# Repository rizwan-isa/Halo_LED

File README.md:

[comment]: <> (GitHub Repository Display Page)
[comment]: <> (Engineering Services Templates)
[comment]: <> (Rizwan Isa, 2024)

# Engineering Services — Project Templates

This repository contains reusable templates, skeletons, and process assets used by **Engineering Services** for delivering professional electronics, PCB, and mechanical CAD projects.

It is intended to:

- standardise project structure across client and personal work
- reduce setup time for new projects
- improve consistency of documentation, reviews, and manufacturing outputs
- make projects easy to navigate, audit, and hand over

---

## What’s Included

### Project Skeletons

Ready-made folder structures for common project types (e.g. hardware PCB project).

### Documentation Templates

Reusable documents for requirements capture, design notes, design reviews, and manufacturing handover.

### Gitignore Templates

Tool-specific `.gitignore` templates (KiCad, Altium, CAD exports) to keep repos clean and professional.

### Checklists

Practical checklists for:

- design readiness
- review readiness
- release readiness / manufacturing handover

---

## How To Use This Repo

### Recommended: Start a New Project From a Skeleton

1. Copy a skeleton into your new project workspace (example below).
2. Create a new Git repository for the project (one repo per project).
3. Commit the initial structure and start work.

Example (hardware PCB project):

```bash
# From your workspace
cp -R ~/EngineeringServices/01_Templates/engineering-services-templates/project_skeletons/hardware_project \
      ~/EngineeringServices/02_Freelance/Client_Project

cd ~/EngineeringServices/02_Freelance/Client_Project
git init
git add .
git commit -m "Initial project structure"
```

# KiCad Template – Local KiBot “Review Datapack” workflow

This repo is set up to generate a **Review Datapack** (PDFs, BoMs, Gerbers, drill files, etc.) using **KiBot**, driven by a **GitHub Actions workflow**.  
You can run the same workflow **locally** using [`act`](https://github.com/nektos/act) (which runs GitHub Actions inside Docker).

This README documents the **exact local workflow** we used, the **diagnostic steps**, and the **fixes** applied so the workflow runs end‑to‑end locally.

---

## Repo layout (relevant bits)

- `.github/workflows/gen_outputs.yml`  
  GitHub Actions workflow that runs KiBot + packages outputs into a datapack.
- `src/config.kibot.yaml`  
  Main KiBot config entrypoint.
- `src/kibot/test.yaml`  
  “Collector” config that imports all outputs. You can comment out imports here to debug.
- `src/kibot/outputs/*.yaml`  
  Individual KiBot output definitions (Gerbers, drill, BoM, PDFs, etc.).
- `KiBotOutput/`  
  Output folder created by the workflow.
- `ReviewDatapack/`  
  Final datapack folder created by the workflow.

---

## Prerequisites (local)

### 1) Docker

- Install Docker Desktop and ensure it’s running.

### 2) act

On macOS:

```bash
brew install act
```

Check it works:

```bash
act --version
docker --version
```

> **Note (Apple Silicon / M1/M2/M3):**  
> `act` may run containers as `arm64` by default. If you ever hit image compatibility issues, you can force:
>
> ```bash
> act --container-architecture linux/amd64 ...
> ```

---

## Quick start (run the workflow locally)

From the repo root:

```bash
act -W .github/workflows/gen_outputs.yml -j GRD
```

Typical useful variations:

```bash
# Re-run without rebuilding everything (often faster)
act -W .github/workflows/gen_outputs.yml -j GRD -r

# If you need amd64 on Apple Silicon
act -W .github/workflows/gen_outputs.yml -j GRD --container-architecture linux/amd64
```

After success, you should have:

- `KiBotOutput/` populated (PDFs, BoMs, Gerbers, drill files, logs, etc.)
- `ReviewDatapack/Datapack_<...>/` populated (packaged datapack structure)

---

## How the KiBot configuration is wired

### Main entrypoint

`src/config.kibot.yaml` imports:

- `kibot/test.yaml`

### Collector / “test” config

`src/kibot/test.yaml` imports many outputs, e.g.

- `outputs/archive_prj.yaml`
- `outputs/drill.yaml`
- `outputs/gerbers.yaml`
- `outputs/pdf_schematic.yaml`
- etc.

**Debug tip:** you can comment out outputs to isolate problems.

Example (disabling 3D output while debugging):

```yaml
import:
  - outputs/pcb_2d.yaml
  # - outputs/pcb_3d.yaml   # disabled for debug
  - outputs/pdf_pcb.yaml
```

---

## Step-by-step diagnostics & fixes (what we actually did)

### Step 1 — Confirm where KiBot logs are written

We saw the workflow failing at:

- **“Copy kibot run log file into Reports folder”**  
  with:
  ```
  cp: cannot stat 'kibot_log.log': No such file or directory
  ```

**Diagnosis commands (local):**

```bash
ls -al
ls -al KiBotOutput || true

# Find any kibot logs/debug output that actually exists
find . -maxdepth 3 -type f \( -iname "*kibot*log*" -o -iname "*kibot*debug*" \) -print
```

What we found:

- `KiBotOutput/kibot_debug.log` existed
- `KiBotOutput/kibot_log.log` did **not** exist yet

**Fix applied (in workflow):**  
Make KiBot write an explicit log file that the later `cp` step expects.

In `.github/workflows/gen_outputs.yml` we ensured the KiBot step includes:

```yaml
additional_args: "-d -vv -L KiBotOutput/kibot_log.log"
```

Now the copy step succeeds because the file exists:

- `KiBotOutput/kibot_log.log`

> If you prefer not to use `-L`, an alternative is redirecting output, e.g.  
> `kibot ... |& tee KiBotOutput/kibot_log.log` (when running KiBot directly).

---

### Step 2 — Diagnose KiBot config errors (missing output type)

We hit this KiBot error in `KiBotOutput/kibot_debug.log`:

```
ERROR: Output `Run KiBot` needs a type
```

That error means:

- KiBot parsed an entry under `outputs:` where `name:` existed but `type:` was missing.

**How we inspected the exact location:**

```bash
# Show the section around the error
nl -ba KiBotOutput/kibot_debug.log | sed -n '460,520p'

# See config/import chain in the log
grep -nE "Using configuration file|Parsing imports|Outputs loaded from" KiBotOutput/kibot_debug.log | tail -n 80
```

**How to find the broken output in your repo:**

```bash
# Search for the output name (example)
grep -RIn "Run KiBot" src/kibot

# Search for any output missing a type (quick manual check)
grep -RIn "^\s*-\s*name:" src/kibot
```

**What to fix:** ensure every output has a `type:`.

Correct pattern:

```yaml
outputs:
  - name: "something"
    type: "pdf" # <- must exist
```

> If you still can’t find it, a YAML indentation error (or accidentally importing a non‑KiBot YAML) can cause odd parsing.  
> In that case, temporarily comment out imports in `src/kibot/test.yaml` until the error disappears, then narrow down.

---

### Step 3 — Fix `upload-artifact` failures when running locally with act

Once the datapack generation was working, the job still failed at:

- **“Archive production artifacts”** using `actions/upload-artifact@v4`

Errors seen included:

- `Unable to get the ACTIONS_RUNTIME_TOKEN env variable`
- `Failed to CreateArtifact ... ECONNREFUSED`

**Root cause:**  
`act` is not GitHub Actions. `upload-artifact` expects GitHub’s artifact service + runtime token, which does not exist locally.

**Fix applied (Option A):**  
Skip the upload step when running under `act` using `env.ACT` (act sets this).

In `.github/workflows/gen_outputs.yml`:

```yaml
- name: Archive production artifacts
  if: ${{ !env.ACT }}
  uses: actions/upload-artifact@v4
  with:
    name: ReviewDatapack
    path: ReviewDatapack
```

✅ With this change, local runs complete successfully and you just take the files from `ReviewDatapack/` yourself.

---

## Common shell gotchas (zsh)

### Inline comments need a space

This fails:

```bash
ls# comment
```

Use:

```bash
ls # comment
```

### Parentheses in `find`

In zsh, parentheses should be escaped:

```bash
find . -maxdepth 3 -type f \( -iname "*kibot*log*" -o -iname "*kibot*debug*" \) -print
```

---

## Where to change things

### Change project metadata used in the workflow

Edit `.github/workflows/gen_outputs.yml` `env:` section, e.g.:

- `BaseFileName`
- `PCBANumber`
- `PCBNumber`
- `Timezone`

### Enable/disable specific KiBot outputs

Edit `src/kibot/test.yaml` import list and comment out modules you don’t want (or while debugging).

---

## Verify outputs

After a local run:

```bash
ls -al KiBotOutput
ls -al ReviewDatapack
```

Typical important files:

- PDFs: schematic / assembly docs
- Manufacturing: gerbers, drill
- BoMs: CSV + HTML
- Logs: `KiBotOutput/kibot_debug.log`, `KiBotOutput/kibot_log.log`

---

## Troubleshooting checklist

1. **Workflow fails copying a file**

- Run `find` to confirm the file exists and path matches.
- Fix the workflow to point at the real file path.

2. **KiBot complains about config**

- Read `KiBotOutput/kibot_debug.log`
- Use `nl -ba ... | sed -n '...p'` around the error
- Narrow down by commenting out imports in `src/kibot/test.yaml`

3. **upload-artifact fails locally**

- Confirm the step is guarded with:
  ```yaml
  if: ${{ !env.ACT }}
  ```

---

## Appendix — Running KiBot manually (optional)

If you want to run KiBot directly (outside GitHub Actions), from repo root:

```bash
kibot -c src/config.kibot.yaml -d -vv -L KiBotOutput/kibot_log.log
```

> This requires KiBot installed on your machine (the workflow does not).

# Local Workflow Notes (Detailed)

This file is a “deep dive” version of the local run instructions from the root README.

## 1) Install tools

### macOS (Homebrew)

```bash
brew install act
brew install --cask docker
```

Start Docker Desktop, then:

```bash
docker info
act --version
```

## 2) Run the GRD job

```bash
act -W .github/workflows/gen_outputs.yml -j GRD
```

## 3) Inspect results

```bash
tree -L 2 KiBotOutput || ls -R KiBotOutput
tree -L 3 ReviewDatapack || ls -R ReviewDatapack
```

## 4) Debug KiBot problems fast

### A) Confirm config + import chain

```bash
grep -nE "Using configuration file|Parsing imports|Outputs loaded from" KiBotOutput/kibot_debug.log | tail -n 80
```

### B) Show the error context

```bash
nl -ba KiBotOutput/kibot_debug.log | sed -n '1,140p'
```

### C) Binary search outputs

Edit `src/kibot/test.yaml` and comment out half the imports; rerun; repeat until you isolate the failing output module.

## 5) Why we skip artifact upload locally

`actions/upload-artifact@v4` needs GitHub’s runtime token and artifact service.  
`act` doesn’t provide that, so we guard the step:

```yaml
if: ${{ !env.ACT }}
```

This is the correct approach for local debug and CI parity:

- CI run on GitHub uploads artifacts
- Local run produces artifacts on disk only

---

## Creating a new project from this template

### Option 1: GitHub UI (recommended)

1. On GitHub, click **Use this template**
2. Create the new repository (e.g. `FFM`)
3. Clone it locally

```bash
git clone <your-new-repo-url>
cd <your-new-repo>
```

4. Initialize/rename the project (this updates filenames AND workflow env vars)

```bash
python3 scripts/init_project.py --name FFM --pcba ES-A00098 --pcb ES-000144
```

5. Commit the changes

```bash
git status
git commit -am "Initialize project FFM from template"
git push
```

### Option 2: GitHub CLI (fast)

```bash
gh repo create FFM --template <ORG>/<TEMPLATE_REPO> --public
git clone <your-new-repo-url>
cd FFM
python3 Scripts/init_project.py --name FFM --pcba ES-A00098 --pcb ES-000144
git commit -am "Initialize project FFM from template"
git push
```

---

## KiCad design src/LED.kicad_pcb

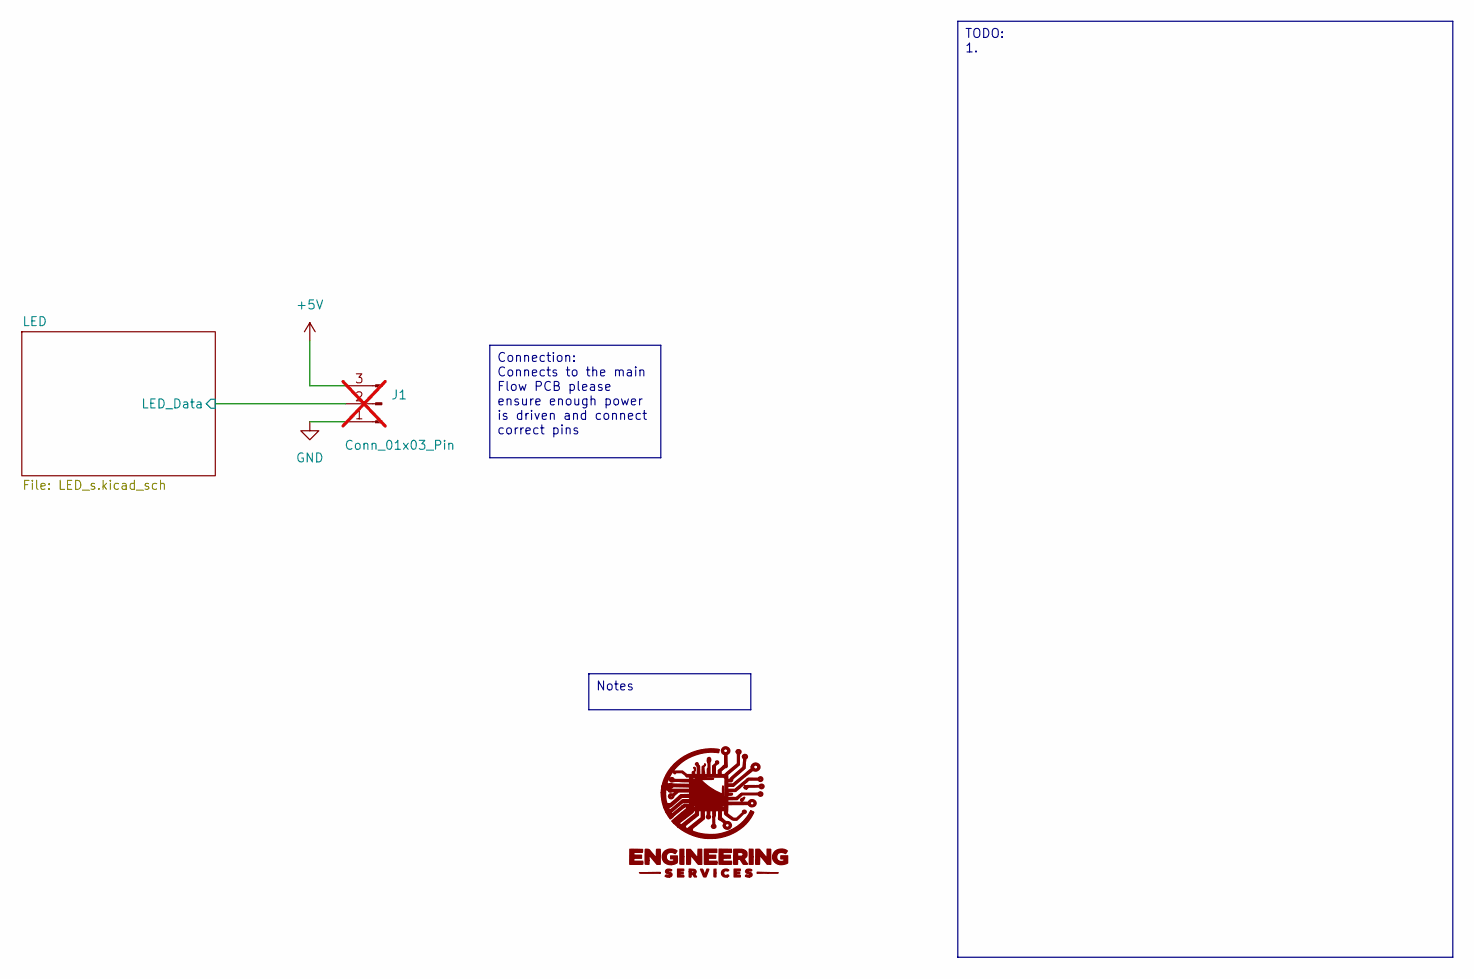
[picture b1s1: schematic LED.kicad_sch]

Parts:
G1: ES_LOGO; ES_logo_30mm_v1
J1: Conn_01x03_Pin; PinSocket_1x03_P1.00mm_Vertical; not fitted

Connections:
+5V: J1.3; also elsewhere on the board
/LED/LED_Data: J1.2; also elsewhere on the board
GND: J1.1; also elsewhere on the board

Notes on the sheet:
TODO: 1.
Connection: Connects to the main Flow PCB please ensure enough power is driven and connect correct pins
Notes

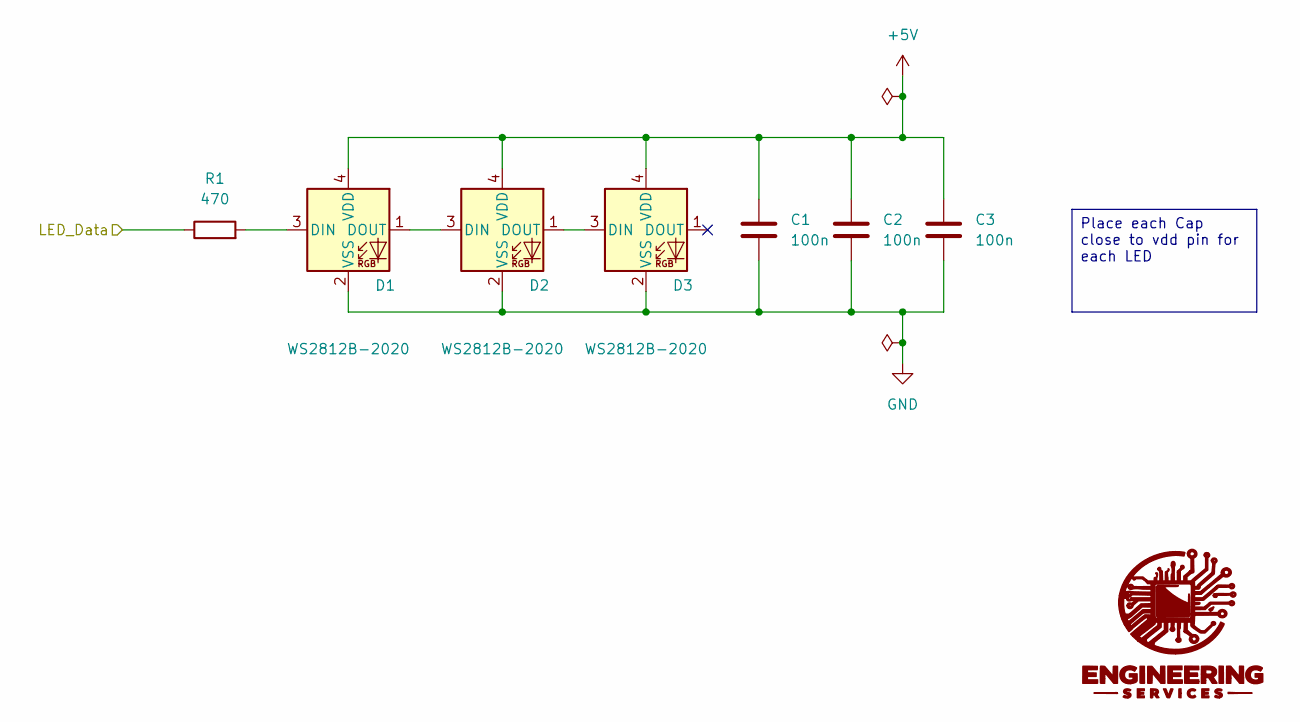
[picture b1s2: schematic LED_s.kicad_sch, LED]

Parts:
C1, C2, C3: 100n; C_0402_1005Metric; MPN CL05B104KO5NNNC; LCSC PN C60474
D1, D2, D3: WS2812B-2020; LED_WS2812B-1.8X2MM; MPN XL-1615RGBC-RF; LCSC PN C3646929
G2: ES_LOGO; ES_logo_30mm_v1
R1: 470; R_0402_1005Metric; MPN AC0402FR-07470RL; LCSC PN C227095

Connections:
+5V: C1.1, C2.1, C3.1, D1.4 (VDD), D2.4 (VDD), D3.4 (VDD); also elsewhere on the board
/LED/LED_Data: R1.1; also elsewhere on the board
GND: C1.2, C2.2, C3.2, D1.2 (VSS), D2.2 (VSS), D3.2 (VSS); also elsewhere on the board
unnamed: D1.3 (DIN), R1.2
unnamed: D1.1 (DOUT), D2.3 (DIN)
unnamed: D2.1 (DOUT), D3.3 (DIN)

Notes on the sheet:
Place each Cap close to vdd pin for each LED

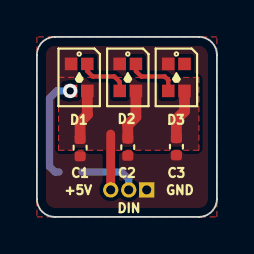
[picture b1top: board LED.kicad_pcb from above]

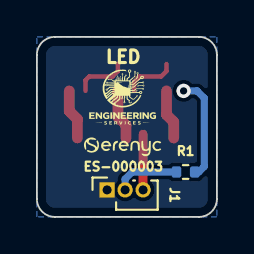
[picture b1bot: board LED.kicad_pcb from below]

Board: 2 copper layers, 10.0 x 10.0 mm, 9 parts (3 on the bottom side), 6 nets.
